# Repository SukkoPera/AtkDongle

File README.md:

# AtkDongle
AtkDongle is an Open Hardware dongle to test and troubleshoot parallel and serial ports on Amiga Computers.

### Summary
While diagnosing faults on Amiga computers, it is necessary to connect a loopback adapter to the serial and parallel ports, which might not be easily available. It might also be necessary to check if the power rails are in order, which involves using multimeter probes directly on the port pins with the risk of creating short-circuits that can damage the machine.

AtkDongle was designed to make these operations easier and safer. It was originally made according to the instructions found in keirf's [Amiga Test Kit](https://github.com/keirf/Amiga-Stuff) (previously known as *SysTest*), but later it was found that Chucky's [DiagROM](http://www.diagrom.com) requires the same connections, thus it is compatible with both of these diagnostic tools.

### Assembly
Solder all components to the board in the order you prefer. Just pay attention to use ports of the right gender on each side, as both connectors are D-Sub 25 pins (*DB-25*) but:
- The **parallel** side needs a **male** connector
- The **serial** side needs a **female** connector

You are also recommended to pay attention to the resistors as you might need to tune them according to the colors and type of leds you are going to use: for instance, I used a red, a yellow and a green led and I had to use resistors of respectively 470, 680 and 220 ohm in order to make them look as bright as each other. Cathode (shorter leg) goes into the square pad.

### Usage
You can plug the dongle into the serial or parallel port of any Amiga at any time. Always use one side at a time: **NEVER connect both ports of the dongle at the same time!**

Some of the leds will light up if the power pins are providing voltage and current. In particular:
- D1 should light up when you connect the dongle to the **parallel** port and the 5V rail is getting power.
- D2 and D3 should light up when you connect the dongle to the **serial** port and the +/-12V rails are getting power, respectively.

A led lighting up does not imply that the corresponding voltage is actually correct, so you should grab your multimeter and make sure by measuring on the exposed pads. Just be careful not to trigger any short-circuit (The +12V pad sits pretty close to a leg of R1, you were warned!).

The dongle also provides loopback connections for both the parallel and serial ports. These are useful for the port tests in Amiga Test Kit (Hit <kbd>F8</kbd>) or DiagROM (Go to *Porttests*, <kbd>5</kbd>).

Finally, you can solder pin headers that will allow easy access to all the voltages present on the ports so that you can use them to power other boards/peripherals. Note that most (if not all) Amiga models limit the current that can be drawn from the ports, so you are recommended to check the Amiga schematics and **NOT to use these if you do not fully understand what you are doing, as you might damage your Amiga and/or power supply. Also DO NOT connect jumper caps on these pins, they are not meant for that!**.

### Releases
If you want to get this board produced, you are recommended to get [the latest release](https://github.com/SukkoPera/AtkDongle/releases) rather than the current git version, as the latter might be under development and is not guaranteed to be working.

Every release is accompanied by its Bill Of Materials (BOM) file and any relevant notes about it, which you are recommended to read carefully.

### License
The AtkDongle documentation, including the design itself, is copyright &copy; SukkoPera 2020.

AtkDongle is Open Hardware licensed under the [CERN OHL v. 1.2](http://ohwr.org/cernohl).

You may redistribute and modify this documentation under the terms of the CERN OHL v.1.2. This documentation is distributed *as is* and WITHOUT ANY EXPRESS OR IMPLIED WARRANTIES whatsoever with respect to its functionality, operability or use, including, without limitation, any implied warranties OF MERCHANTABILITY, SATISFACTORY QUALITY, FITNESS FOR A PARTICULAR PURPOSE or infringement. We expressly disclaim any liability whatsoever for any direct, indirect, consequential, incidental or special damages, including, without limitation, lost revenues, lost profits, losses resulting from business interruption or loss of data, regardless of the form of action or legal theory under which the liability may be asserted, even if advised of the possibility or likelihood of such damages.

A copy of the full license is included in file [LICENSE.pdf](LICENSE.pdf), please refer to it for applicable conditions. In order to properly deal with its terms, please see file [LICENSE_HOWTO.pdf](LICENSE_HOWTO.pdf).

The contact points for information about manufactured Products (see section 4.2) are listed in file [PRODUCT.md](PRODUCT.md).

Any modifications made by Licensees (see section 3.4.b) shall be recorded in file [CHANGES.md](CHANGES.md).

The Documentation Location of the original project is https://github.com/SukkoPera/AtkDongle/.

### Support the Project
Since the project is open you are free to get the PCBs made by your preferred manufacturer, however in case you want to support the development, you can order them from PCBWay through this link:

You get my gratitude and cheap, professionally-made and good quality PCBs, I get some credit that will help with this and [other projects](https://www.pcbway.com/project/member/shareproject/?bmbid=41100). You won't even have to worry about the various PCB options, it's all pre-configured for you!

Also, if you still have to register to that site, [you can use this link](https://www.pcbway.com/setinvite.aspx?inviteid=41100) to get some bonus initial credit (and yield me some more).

Again, if you want to use another manufacturer, feel free to, don't feel obligated :). But then you can buy me a coffee if you want:

### Get Help
If you need help or have questions, you can join [the official Telegram group](https://t.me/joinchat/HUHdWBC9J9JnYIrvTYfZmg).

### Thanks
- [keirf](https://github.com/keirf) for Amiga Test Kit
- Chucky for DiagROM

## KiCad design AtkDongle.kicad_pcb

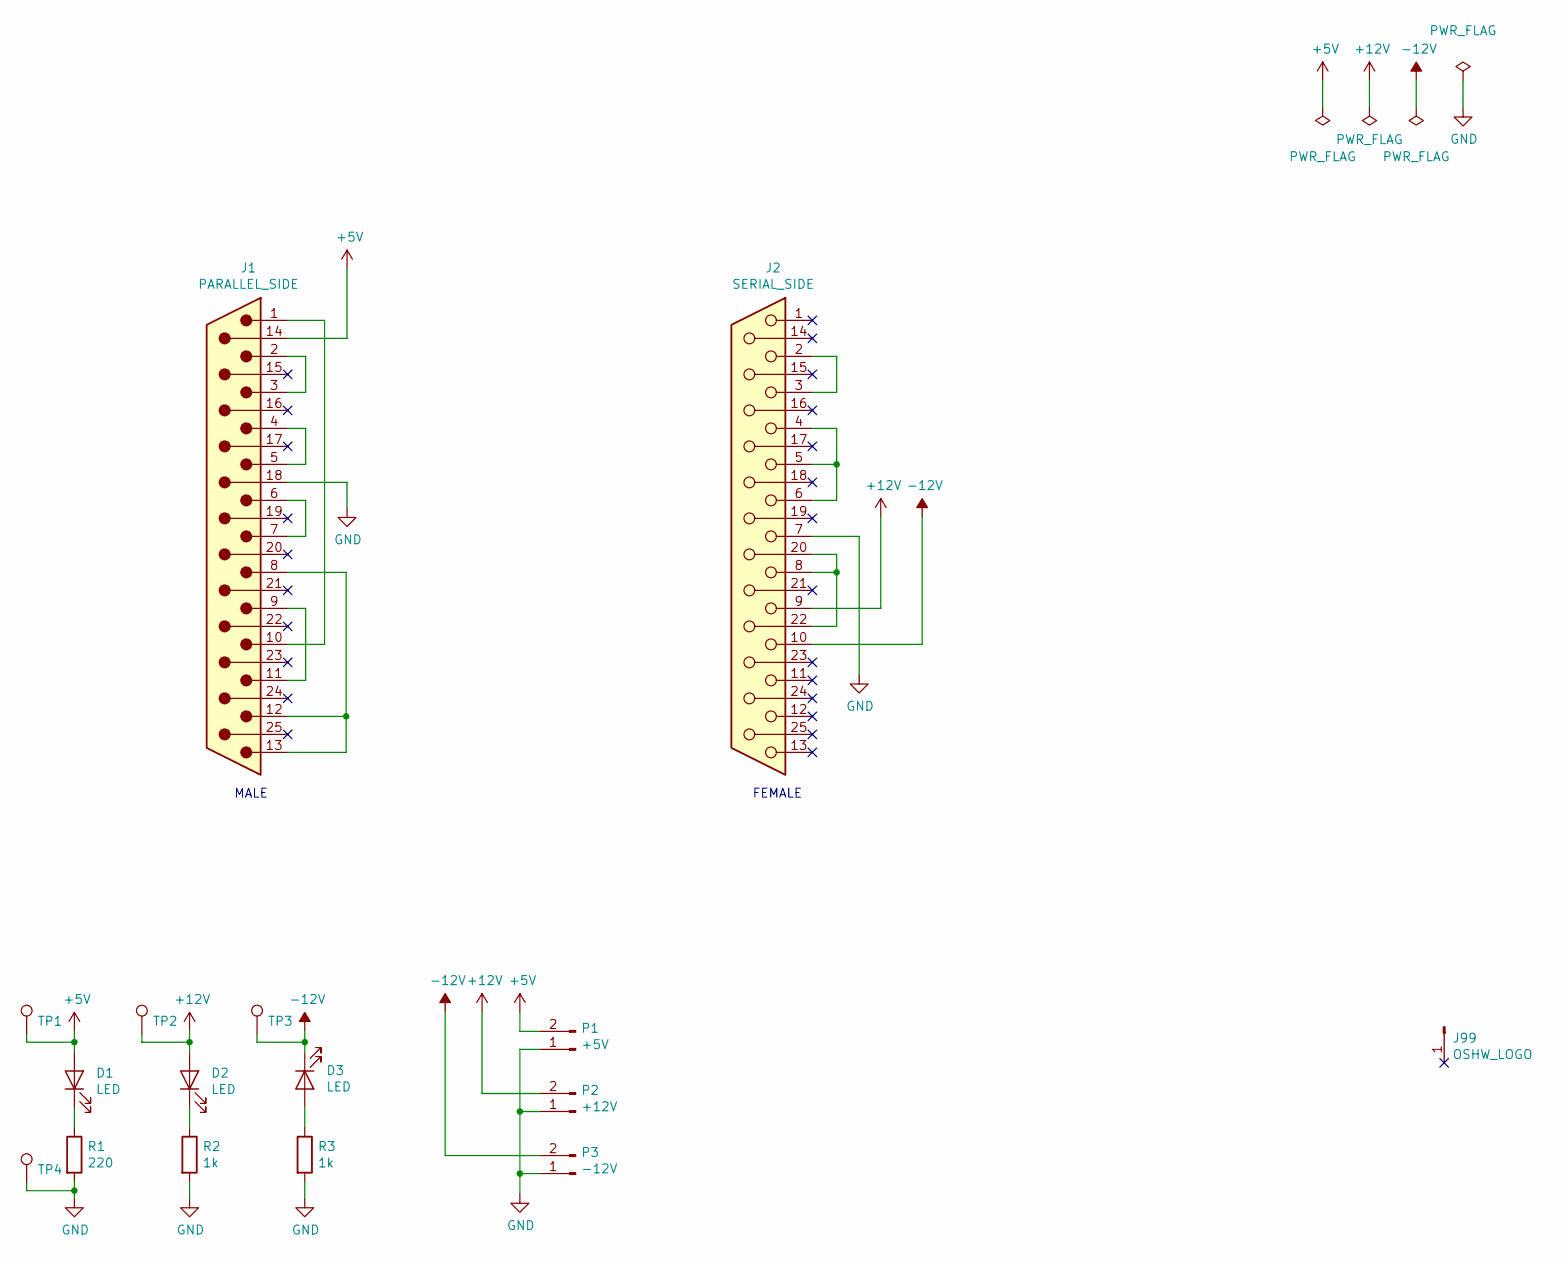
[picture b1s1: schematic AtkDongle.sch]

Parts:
D1, D2, D3: LED; LED_D3.0mm
J1: PARALLEL_SIDE; DSUB-25_Male_EdgeMount_P2.77mm
J2: SERIAL_SIDE; DSUB-25_Female_EdgeMount_P2.77mm
J99: OSHW_LOGO; OSHW-Logo2_7.3x6mm_Copper
P1: +5V; PinHeader_1x02_P2.54mm_Vertical
P2: +12V; PinHeader_1x02_P2.54mm_Vertical
P3: -12V; PinHeader_1x02_P2.54mm_Vertical
R1: 220; R_Axial_DIN0207_L6.3mm_D2.5mm_P10.16mm_Horizontal
R2, R3: 1k; R_Axial_DIN0207_L6.3mm_D2.5mm_P10.16mm_Horizontal
TP1: TP+5V; TestPoint_Pad_D2.0mm
TP2: TP+12V; TestPoint_Pad_D2.0mm
TP3: TP-12V; TestPoint_Pad_D2.0mm
TP4: TPGND; TestPoint_Pad_D2.0mm

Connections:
+5V: D1.2 (A), J1.14, P1.2, TP1.1
+12V: D2.2 (A), J2.9, P2.2, TP2.1
-12V: D3.1 (K), J2.10, P3.2, TP3.1
GND: J1.18, J2.7, P1.1, P2.1, P3.1, R1.2, R2.2, R3.2, TP4.1
unnamed: D1.1 (K), R1.1
unnamed: D2.1 (K), R2.1
unnamed: D3.2 (A), R3.1
unnamed: J1.1, J1.10
unnamed: J1.2, J1.3
unnamed: J1.4, J1.5
unnamed: J1.6, J1.7
unnamed: J1.9, J1.11
unnamed: J1.8, J1.12, J1.13
unnamed: J2.2, J2.3
unnamed: J2.4, J2.5, J2.6
unnamed: J2.8, J2.20, J2.22

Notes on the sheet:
MALE
FEMALE

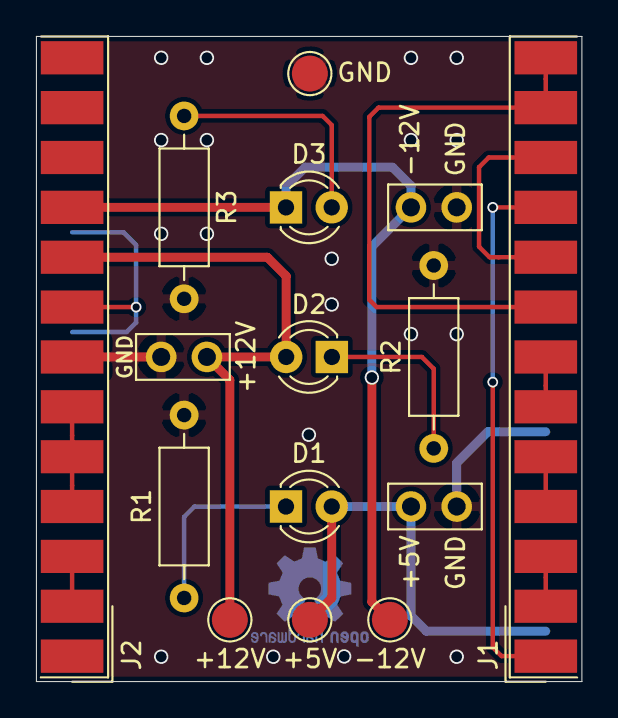
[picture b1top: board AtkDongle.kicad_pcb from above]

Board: 2 copper layers, 30.3 x 35.8 mm, 16 parts (1 on the bottom side), 16 nets.

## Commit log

2020-01-01 Remove redundant directory
2020-01-01 Fix silkscreen
2020-01-02 Ready for prototypes!
2020-02-12 Add license
2020-02-13 Add README
2020-03-20 Add fp-info-cache to .gitignore
2020-03-20 Remove fp-info-cache
2020-03-20 Update info about compatibility with DiagROM in README
2020-03-20 Typo

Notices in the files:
AtkDongle.kicad_pcb:
Licensed under CERN OHL v.1.2
